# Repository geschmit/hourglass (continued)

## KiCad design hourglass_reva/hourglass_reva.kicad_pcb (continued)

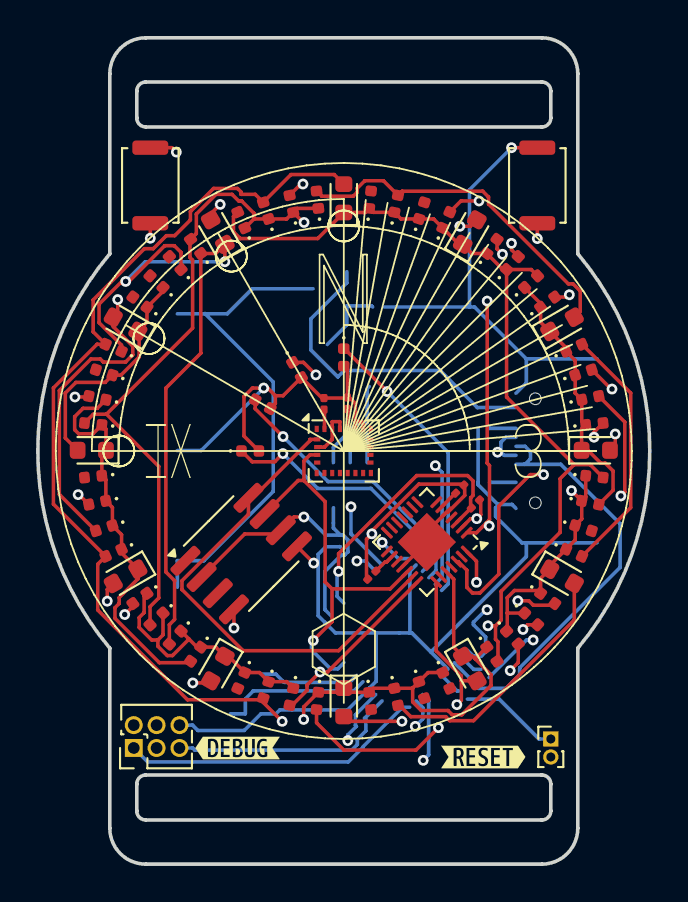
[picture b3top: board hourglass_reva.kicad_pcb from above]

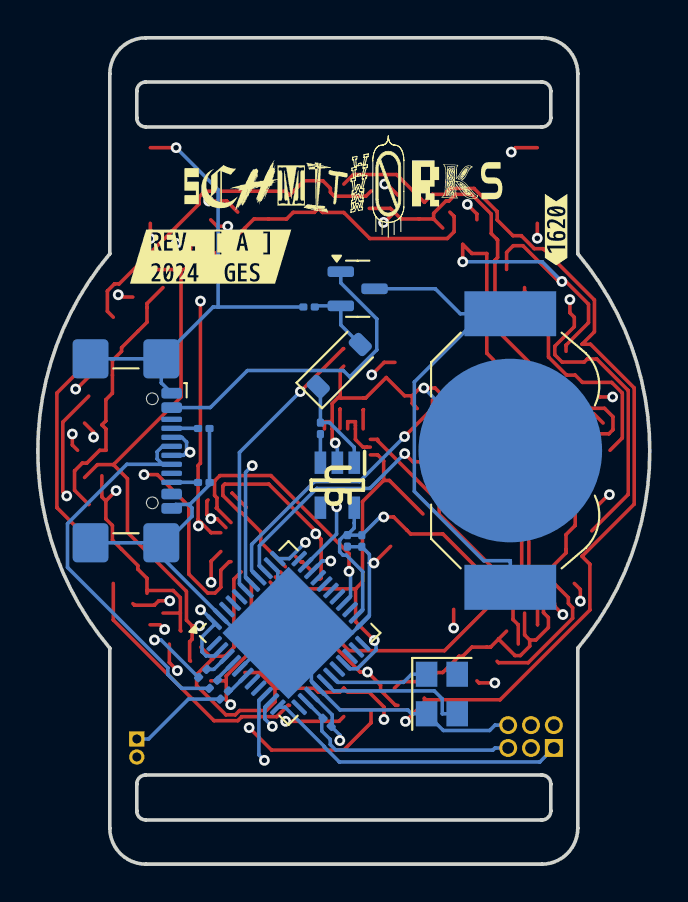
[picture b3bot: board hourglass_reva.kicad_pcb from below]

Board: 4 copper layers, 34.0 x 45.9 mm, 97 parts (19 on the bottom side), 42 nets.

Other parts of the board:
kibuzzard-66A6C66D: G***; kibuzzard-66A6C66D
kibuzzard-66A6C661: G***; kibuzzard-66A6C661
kibuzzard-66A7D7EA: G***; kibuzzard-66A7D7EA
kibuzzard-66A7EADD: G***; kibuzzard-66A7EADD
